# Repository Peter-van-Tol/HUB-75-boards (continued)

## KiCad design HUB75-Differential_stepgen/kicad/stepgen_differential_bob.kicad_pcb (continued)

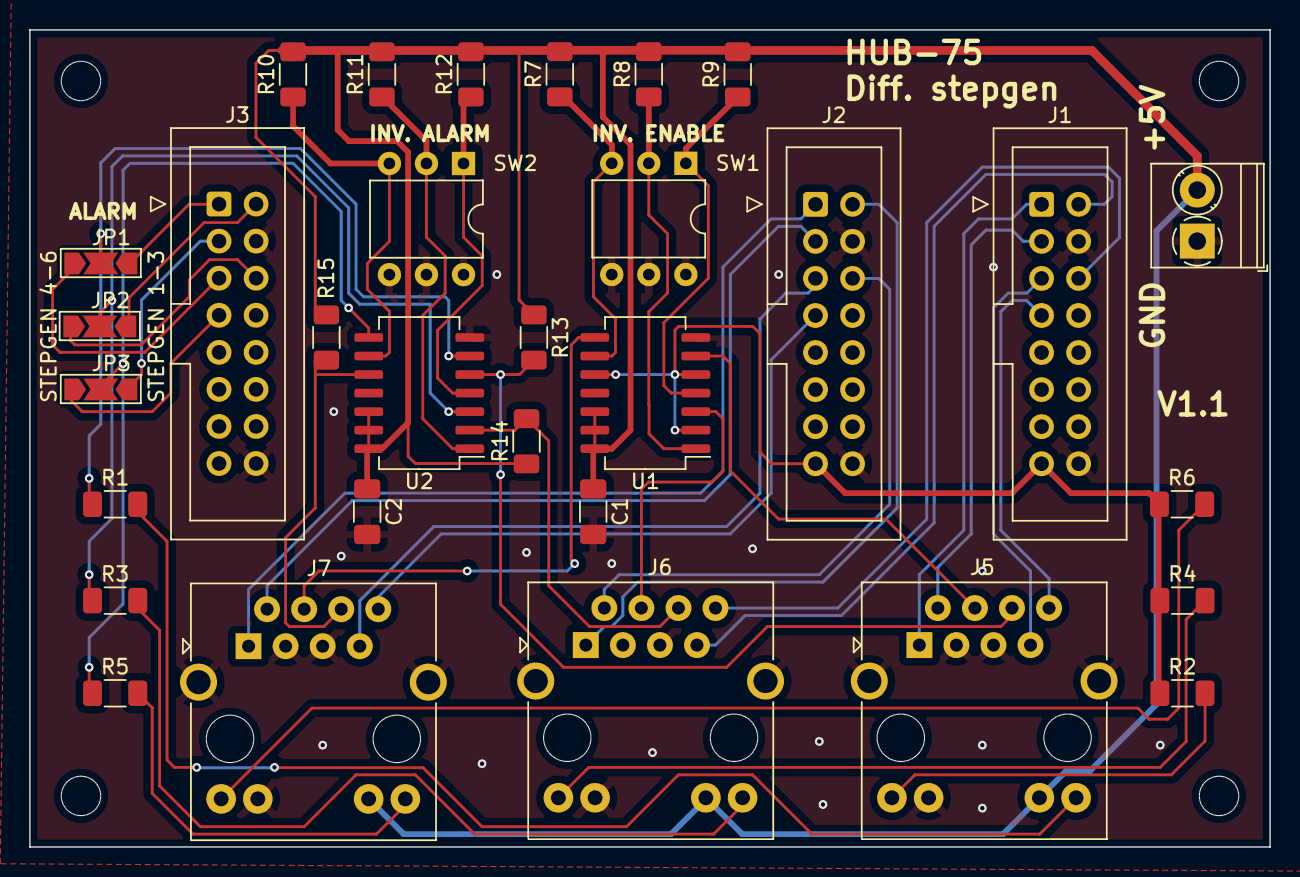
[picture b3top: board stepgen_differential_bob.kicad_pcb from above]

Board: 2 copper layers, 85.0 x 56.0 mm, 35 parts (0 on the bottom side), 42 nets.

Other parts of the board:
Hole1, Hole2, Hole3, Hole4: MountingHole_2.7mm_M2.5_DIN965

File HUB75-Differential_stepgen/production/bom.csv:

Designator,Footprint,Quantity,Value,LCSC Part #
"C1, C2",C_1206_3216Metric_Pad1.33x1.80mm_HandSolder,2,100nF,
"J1, J2, J3",IDC-Header_2x08_P2.54mm_Vertical,3,Conn_02x08_Odd_Even,
J4,"TerminalBlock_Phoenix_PT-1,5-2-3.5-H_1x02_P3.50mm_Horizontal",1,Screw_Terminal_01x02,
"J5, J6, J7",RJ45_BEL_SS74301-00x_Vertical,3,RJ45_LED,
"JP1, JP2, JP3",SolderJumper-3_P2.0mm_Open_TrianglePad1.0x1.5mm_NumberLabels,3,SolderJumper_3_Bridged123,
"R1, R2, R3, R4, R5, R6",R_1206_3216Metric_Pad1.30x1.75mm_HandSolder,6,270,
"R10, R11, R12, R13, R14, R15, R7, R8, R9",R_1206_3216Metric_Pad1.30x1.75mm_HandSolder,9,10k,
"SW1, SW2",DIP-6_W7.62mm,2,SW_DIP_x03,
"U1, U2",SO-14_5.3x10.2mm_P1.27mm,2,74HC86,

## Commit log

2022-11-14 Initial commit
    License from https://github.com/santisoler/cc-licenses/blob/main/LICENSE-CC-BY-NC-SA
2022-11-14 Update layout
2022-11-15 Clarify license
2022-11-15 Add changing board
2022-11-15 Added datasheet
2022-11-16 Proto-type production ready
2022-11-16 Moved license logo + added name
2022-11-17 Update board with current mirror + backup
2022-11-17 Update label
2022-11-17 Production files v1.0
2022-11-17 Update part number
2022-11-17 Remove incorrect GND connection
2022-11-17 Smaller resistors + production ready
2022-11-20 Change trace width
2022-11-20 Add cache
2022-11-20 Remove autosave
2022-11-20 Moved design to correct folder
2022-11-20 Remove autosave file from repo
2022-11-20 Update BOM and images
2022-11-20 Added production files
2022-11-20 Regenerated
2022-11-20 Updated minimum size and added tables
2022-12-01 Corrected part list
    Added missing decoupling capacitors
    Corrected serial number of the XOR-gate
2022-12-01 Update to v1.1 after prototype
2022-12-01 New render with IDC-connectors
2022-12-02 New version after prototype failed
2022-12-02 Updated status
2022-12-02 Version for prototype
